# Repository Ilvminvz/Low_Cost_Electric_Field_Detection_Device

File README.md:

This contains the LaTeX documentation, KiCad schematics, and fabrication of the Electric Field Detection device.

This project is released under the CERN Open Hardware Licence v2 – Permissive (CERN-OHL-P).
See the LICENSE file for details.

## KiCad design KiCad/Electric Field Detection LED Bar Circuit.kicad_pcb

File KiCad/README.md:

This directory contains the KiCad PCB design and the Schematics of the Atmega board and the LED Bar

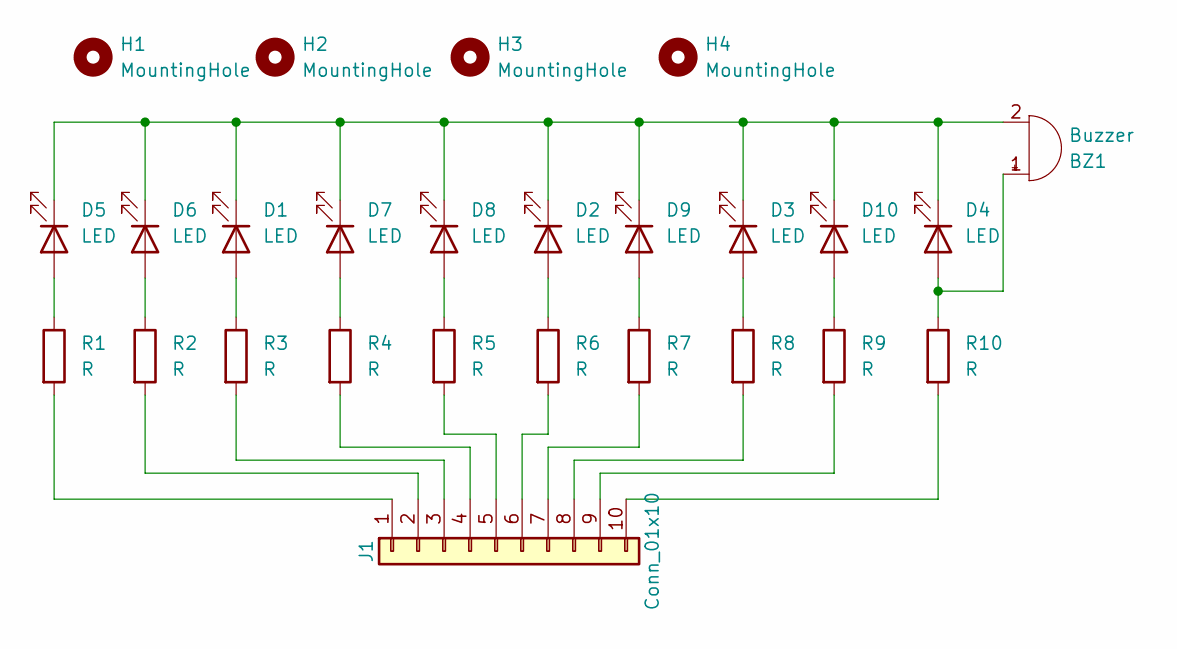
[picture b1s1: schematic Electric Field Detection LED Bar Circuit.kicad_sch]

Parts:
BZ1: Buzzer; MagneticBuzzer_Kingstate_KCG0601
D1, D5, D6, D7: LED; LED_VCCLite_5381H5_6.35x6.35mm
D2, D3, D8, D9: LED; LED_VCCLite_5381H7_6.35x6.35mm
D4, D10: LED; LED_VCCLite_5381H1_6.35x6.35mm
H1, H2, H3, H4: MountingHole; MountingHole_2.1mm
J1: Conn_01x10; PinSocket_1x10_P2.00mm_Vertical
R1, R2, R3, R4, R5, R6, R7, R8, R9, R10: R; R_Axial_DIN0207_L6.3mm_D2.5mm_P7.62mm_Horizontal

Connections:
unnamed: BZ1.1 (+), D4.2 (A), R10.1
unnamed: BZ1.2 (-), D1.1 (K), D2.1 (K), D3.1 (K), D4.1 (K), D5.1 (K), D6.1 (K), D7.1 (K), D8.1 (K), D9.1 (K), D10.1 (K)
unnamed: D1.2 (A), R3.1
unnamed: D2.2 (A), R6.1
unnamed: D3.2 (A), R8.1
unnamed: D5.2 (A), R1.1
unnamed: D6.2 (A), R2.1
unnamed: D7.2 (A), R4.1
unnamed: D8.2 (A), R5.1
unnamed: D9.2 (A), R7.1
unnamed: D10.2 (A), R9.1
unnamed: J1.1, R1.2
unnamed: J1.2, R2.2
unnamed: J1.3, R3.2
unnamed: J1.4, R4.2
unnamed: J1.5, R5.2
unnamed: J1.6, R6.2
unnamed: J1.7, R7.2
unnamed: J1.8, R8.2
unnamed: J1.9, R9.2
unnamed: J1.10, R10.2

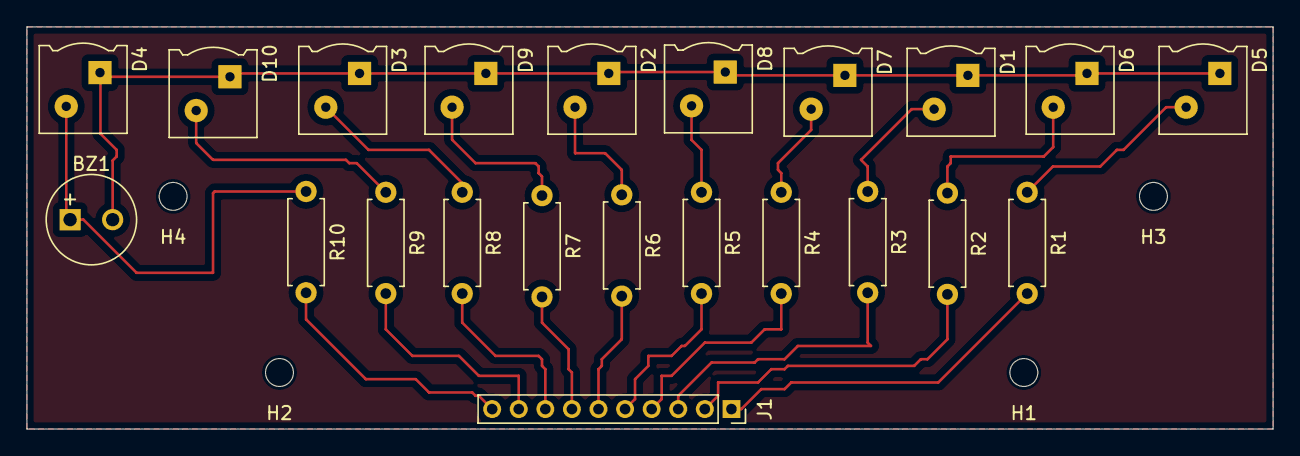
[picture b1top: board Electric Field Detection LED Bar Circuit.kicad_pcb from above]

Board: 2 copper layers, 93.8 x 30.2 mm, 26 parts (0 on the bottom side), 21 nets.

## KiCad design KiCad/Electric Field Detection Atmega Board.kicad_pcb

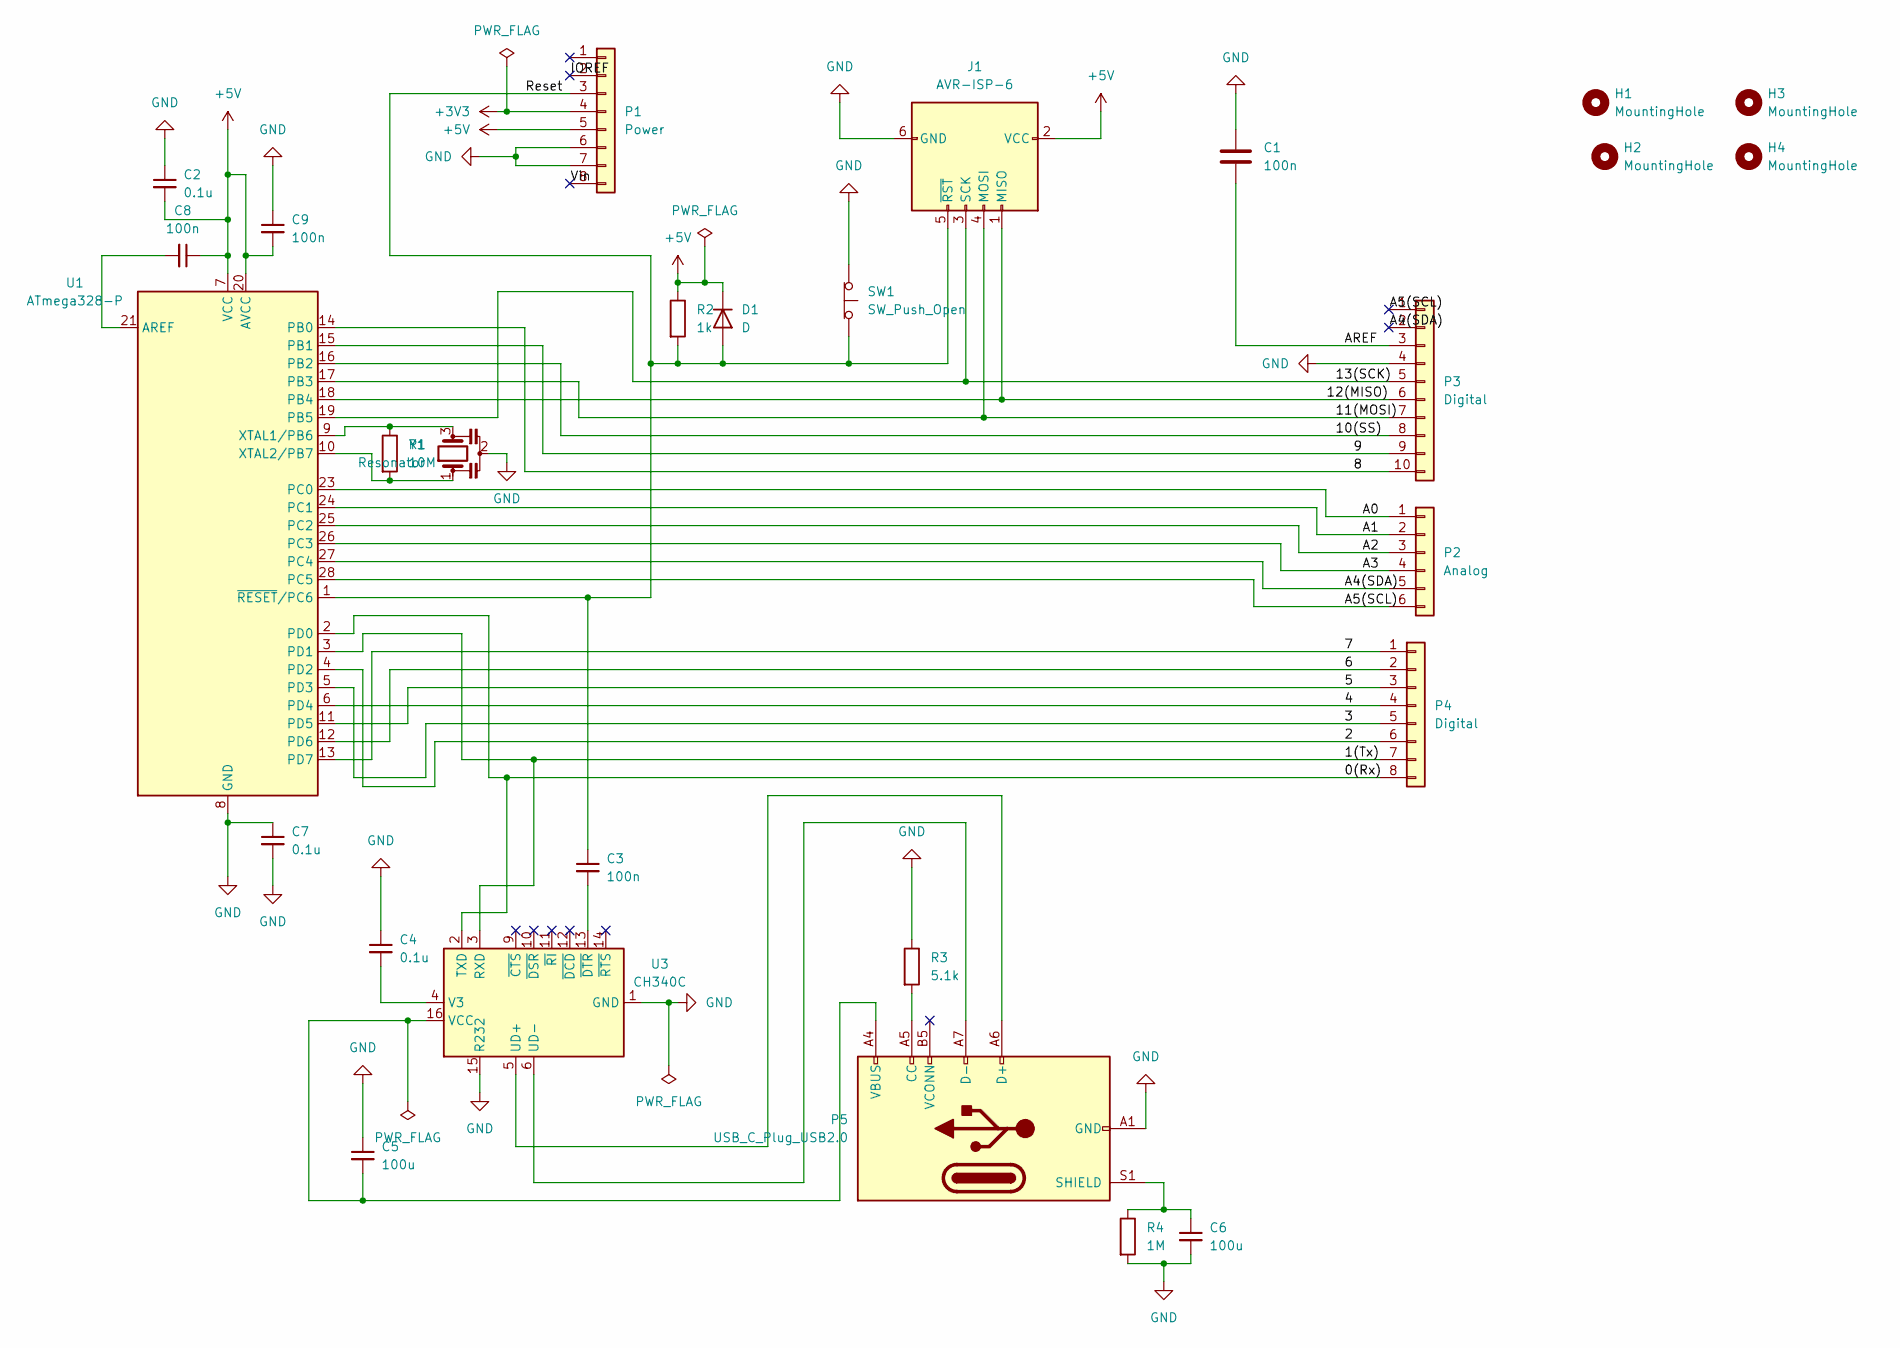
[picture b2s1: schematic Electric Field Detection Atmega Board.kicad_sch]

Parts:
C1, C3, C8, C9: 100n; C_Axial_L3.8mm_D2.6mm_P7.50mm_Horizontal
C2, C4, C7: 0.1u; C_Axial_L3.8mm_D2.6mm_P7.50mm_Horizontal
C5, C6: 100u; C_Axial_L3.8mm_D2.6mm_P7.50mm_Horizontal
D1: D; D_DO-35_SOD27_P7.62mm_Horizontal
H1, H2, H3, H4: MountingHole; MountingHole_2.1mm
J1: AVR-ISP-6; IDC-Header_2x03_P2.54mm_Vertical
P1: Power; PinSocket_1x08_P2.00mm_Vertical
P2: Analog; PinSocket_1x06_P2.00mm_Vertical
P3: Digital; PinSocket_1x10_P2.00mm_Vertical
P4: Digital; PinSocket_1x08_P2.00mm_Vertical
P5: USB_C_Plug_USB2.0; USB_C_Plug_ShenzhenJingTuoJin_918-118A2021Y40002_Vertical
R1: 10M; R_Axial_DIN0207_L6.3mm_D2.5mm_P10.16mm_Horizontal
R2: 1k; R_Axial_DIN0204_L3.6mm_D1.6mm_P7.62mm_Horizontal
R3: 5.1k; R_Axial_DIN0207_L6.3mm_D2.5mm_P10.16mm_Horizontal
R4: 1M; R_Axial_DIN0204_L3.6mm_D1.6mm_P7.62mm_Horizontal
SW1: SW_Push_Open; SW_PUSH_6mm_H4.3mm
U1: ATmega328-P; DIP-28_W7.62mm
U3: CH340C; SOIC-16_3.9x9.9mm_P1.27mm
Y1: Resonator; Resonator_Murata_CSTLSxxxX-3Pin_W5.5mm_H3.0mm

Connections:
+3V3: P1.4
+5V: C2.2, C8.1, C9.2, D1.1 (K), J1.2 (VCC), P1.5, R2.1, U1.7 (VCC), U1.20 (AVCC)
/0(Rx): P4.8, U1.2 (PD0), U3.2 (TXD)
/1(Tx): P4.7, U1.3 (PD1), U3.3 (RXD)
/2: P4.6, U1.4 (PD2)
/3: P4.5, U1.5 (PD3)
/4: P4.4, U1.6 (PD4)
/5: P4.3, U1.11 (PD5)
/6: P4.2, U1.12 (PD6)
/7: P4.1, U1.13 (PD7)
/8: P3.10, U1.14 (PB0)
/9: P3.9, U1.15 (PB1)
/10(SS): P3.8, U1.16 (PB2)
/11(MOSI): J1.4 (MOSI), P3.7, U1.17 (PB3)
/12(MISO): J1.1 (MISO), P3.6, U1.18 (PB4)
/13(SCK): J1.3 (SCK), P3.5, U1.19 (PB5)
/A0: P2.1, U1.23 (PC0)
/A1: P2.2, U1.24 (PC1)
/A2: P2.3, U1.25 (PC2)
/A3: P2.4, U1.26 (PC3)
/A4(SDA): P2.5, P3.2, U1.27 (PC4)
/A5(SCL): P2.6, P3.1, U1.28 (PC5)
/AREF: C1.2, P3.3
/IOREF: P1.2
/Reset: C3.1, D1.2 (A), J1.5 (~RST), P1.3, R2.2, SW1.2 (B), U1.1 (~RESET/PC6)
/Vin: P1.8
GND: C1.1, C2.1, C4.1, C5.1, C6.2, C7.1, C7.2, C9.1, J1.6 (GND), P1.6, P1.7, P3.4, P5.A1 (GND), P5.A12 (GND), P5.B1 (GND), P5.B12 (GND), R3.1, R4.2, SW1.1 (A), U1.8 (GND), U1.22 (GND), U3.1 (GND), U3.15 (R232), Y1.2
unnamed: P5.A5 (CC), R3.2
unnamed: P5.A6 (D+), U3.5 (UD+)
unnamed: P5.A7 (D-), U3.6 (UD-)
unnamed: C6.1, P5.S1 (SHIELD), R4.1
unnamed: C8.2, U1.21 (AREF)
unnamed: R1.1, U1.9 (XTAL1/PB6), Y1.3
unnamed: R1.2, U1.10 (XTAL2/PB7), Y1.1
unnamed: C4.2, U3.4 (V3)
unnamed: C5.2, P5.A4 (VBUS), P5.A9 (VBUS), P5.B4 (VBUS), P5.B9 (VBUS), U3.16 (VCC)
unnamed: C3.2, U3.13 (~DTR)

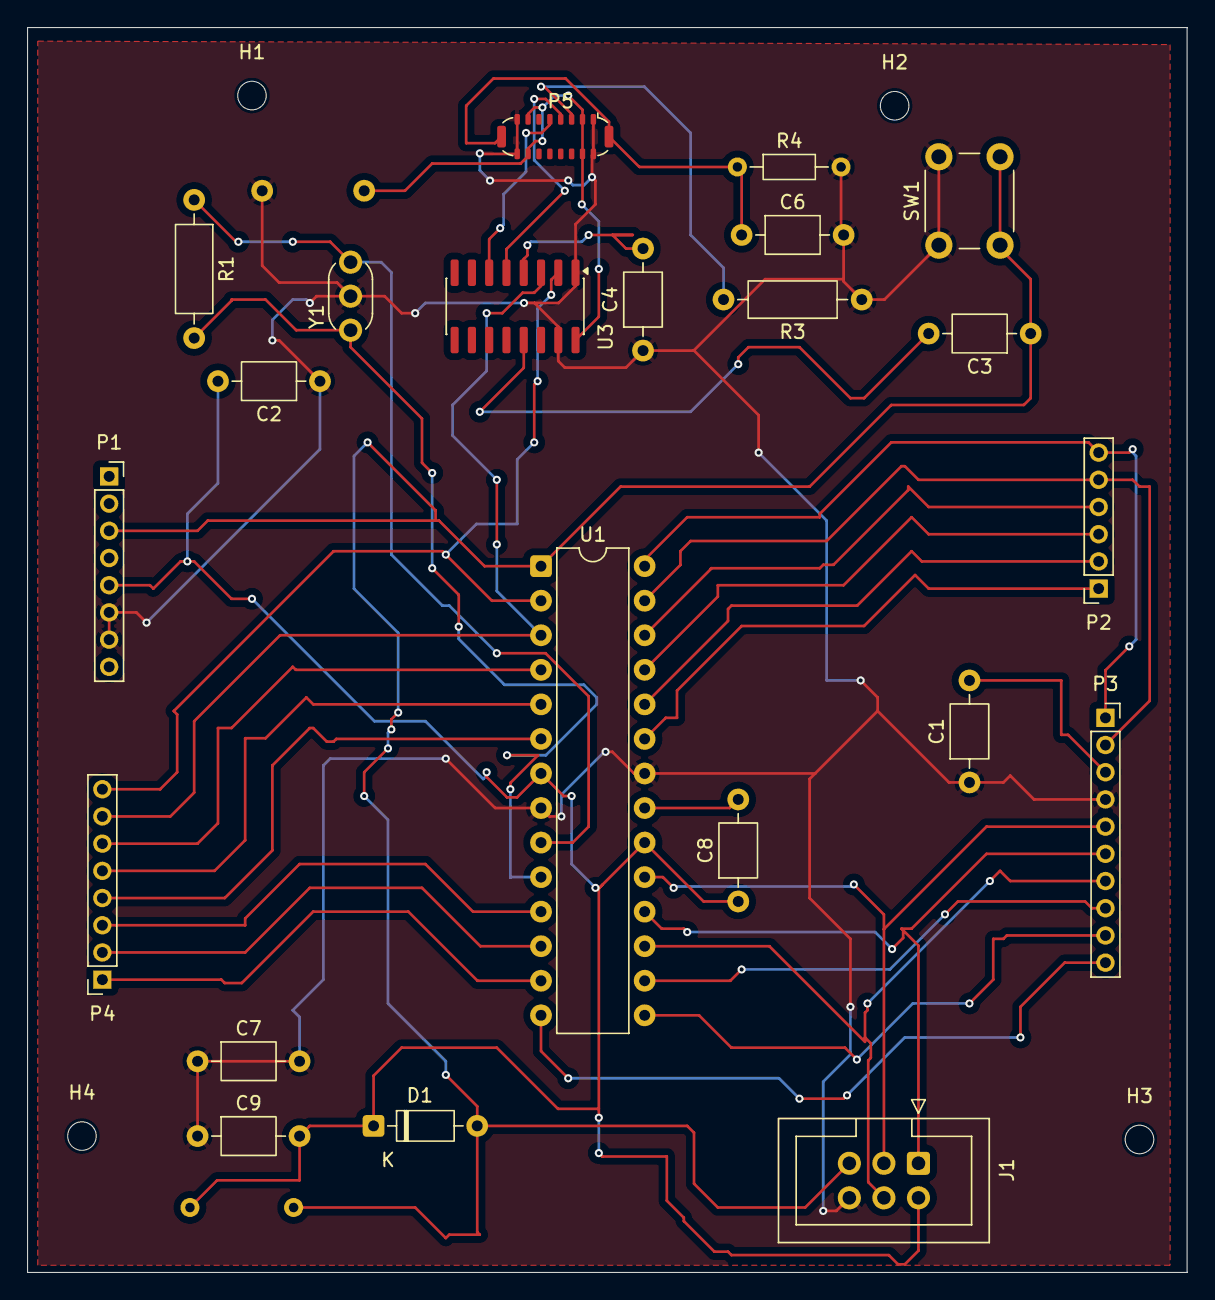
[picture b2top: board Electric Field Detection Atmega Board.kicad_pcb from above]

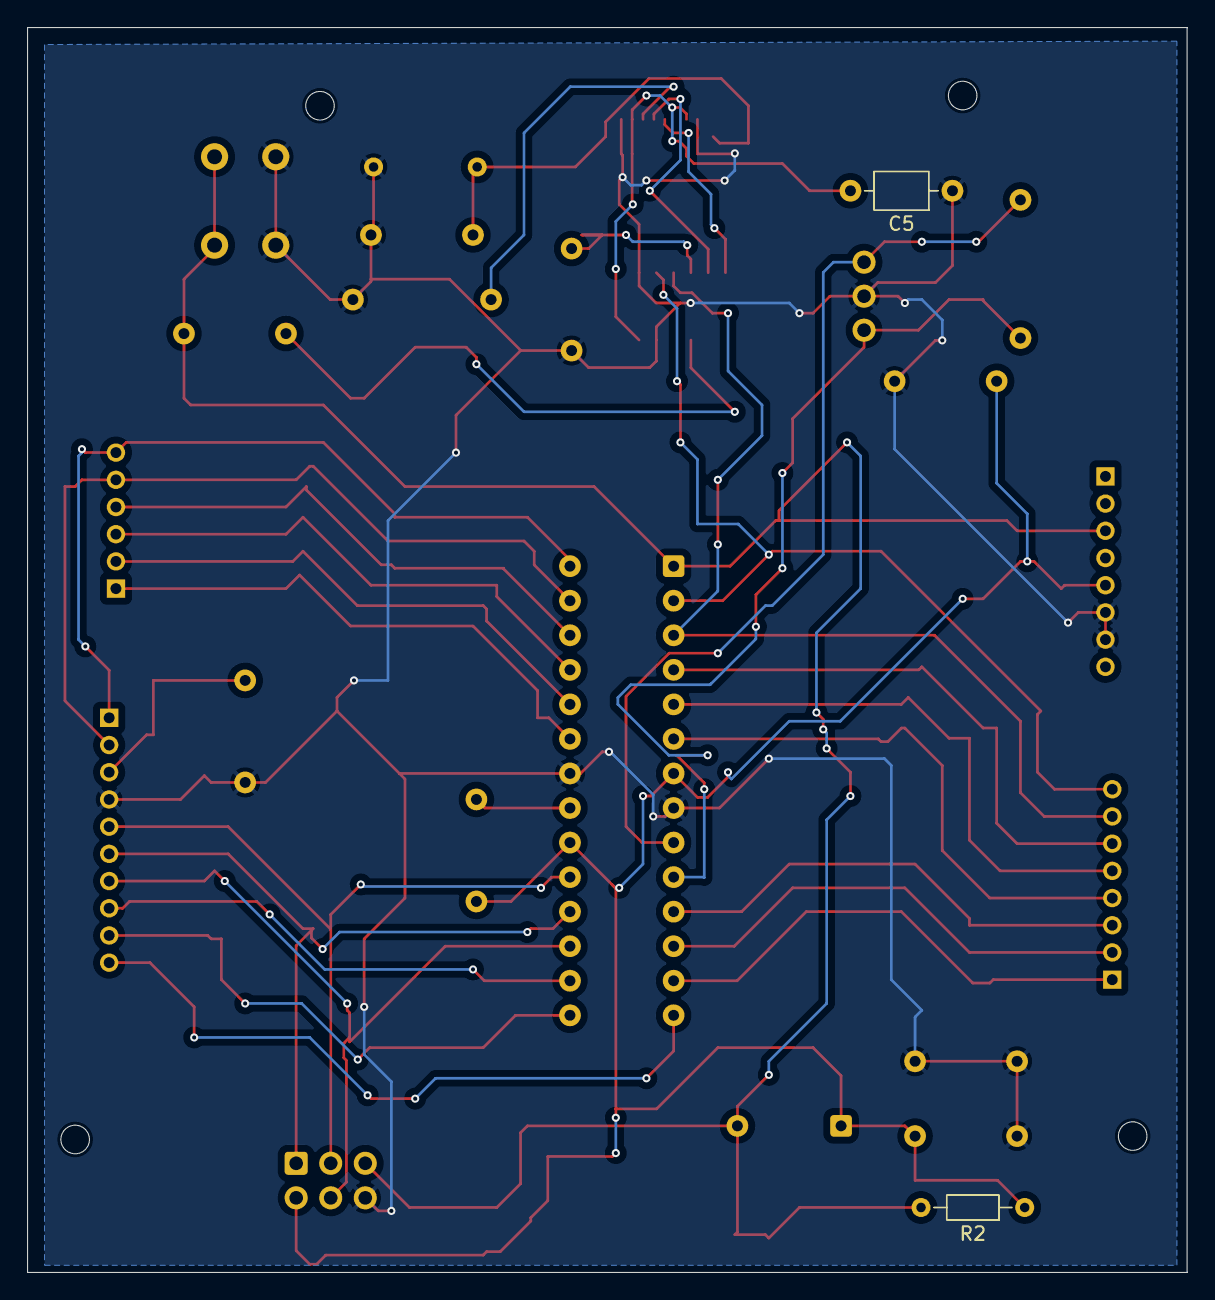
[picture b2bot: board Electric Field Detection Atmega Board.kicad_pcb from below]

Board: 2 copper layers, 85.2 x 91.5 mm, 28 parts (2 on the bottom side), 34 nets.

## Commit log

2026-01-19 Create LICENSE
